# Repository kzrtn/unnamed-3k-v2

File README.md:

# unnamed-3k-v2 keypad
 A simple 3 key mechanical hotswap keypad for osu! Uses an Atmega32u2 (also compatible with Atmega16u2). Created using Kicad and AutoCad/Coreldraw.

 ## IMPORTANT
 This uploaded version of the keypad is **slightly changed** from the prototype in the pictures above.
 
 **Changes:**
 - Removed in-key LEDs
 - Changed north facing switches to south facing
 - Switch pins were changed from B4, B6, B7 to B7, C7, C6
 - Removed unnecessary vias.

This means that what is put up here is **untested**. However if you've tried producing this and everything checks out (it should, changes were very minor) please send me an email at `jolene.tkk@gmail.com` or contact me somehow. I'll update this page and/or fix any issues raised.
 
 ## Features
 - Cherry MX hotswap
 - Uses QMK and has VIA (sort of)
 - 1000hz, chordsplits at 1ms
 - Acrylic sandwich
 - RGB underglow

**Notes regarding QMK and VIA:**

This is not pushed into QMK or VIA's repo. QMK source files are found in the firmware folder. To use VIA with the keypad, go to `settings tab in the VIA software > enable 'Show Design Tab > go to Design tab > Load Draft Definition > Upload the 'load_in_VIA.json' file from qmk-unnamed3kv2-source folder`. **You will have to do this each time you want to use VIA**.

## Settings and RGB modes
Upon plugging in, you will be booted into **Layer 0** where it outputs Z, X and C (play mode). To change RGB modes, hold down the first button (first button on the far left) while plugging in the keypad. It will boot into **Layer 1**.
### Layer 0
| First key  | Second key | Third key |
| ------------- | ------------- |------------- |
| Z | X  | C |
### Layer 1
| First key  | Second key | Third key |
| ------------- | ------------- |------------- |
| Change RGB Mode | Toggle RGB on/off | Go to Layer 2 |
### Layer 2
| First key  | Second key | Third key |
| ------------- | ------------- |------------- |
| Hue value + | Hue value - | Go to Layer 3 |
### Layer 3
| First key  | Second key | Third key |
| ------------- | ------------- |------------- |
| Sat value + | Sat value - | Go to Layer 4 |
### Layer 4
| First key  | Second key | Third key |
| ------------- | ------------- |------------- |
| Brightness value + | Brightness value - | Go to Layer 0 |

**RGB MODES**

- Breathing
- Rainbow mood
- Rainbow swirl
- Static

## Required parts
- PCB with components
- Laser cut acrylic
- 4 x M2 17mm hex stands
- 8 x M2 screws
- (optional) Rubber feet

## PCB assembly tips

The BOM and POS files in `PCB files/Gerber and JLCPCB files` are generated for easy ordering from [JLCPCB](https://jlcpcb.com/). For any parts that are unavailable, especially the crystal and/or the capacitors for the crystal, choose something else that's also 16Mhz with another capacitive load value that's available. Calculate the new values for the caps of the new crystal accordingly using this formula:
```
CL = ((CX1 x CX2) / (CX1 + CX2)) + Cstray

CL: The crystal load capacitance
CX1: The first capacitor
CX2: The second capacitor
Cstray: The stray capacitance in the oscillator circuit, which will normally be in the 2pF to 5pF range.

Assuming that CX1=CX2 then the equation becomes:

CL = ((CX1 x CX1) / (2 x CX1)) + Cstray

CL = (CX1 / 2) + Cstray

Rearranging the equation, we can find the external load capacitor value:

CX1 = 2(CL - Cstray)

For example, if the crystal load capacitance is 15pF, and assuming Cstray=2pF, then:

CX1 = CX2 = 2(15pF - 2pF) = 26pF
```

In the event that you would like to use an **atmega16u2** instead of atmega32u2, you can just do that, no PCB edits is required. But please read the firmware notes section of this readme to adjust the firmware accordingly.

| Part name  | Package type | Notes |
| ------------- | ------------- |------------- |
| Crystal  | SMD3225-4P  | 16MHz is REQUIRED |
| Capacitors  | 0805  |  |
| Resistors | 0805 | |
| Fuse | 1206 | [This](https://lcsc.com/product-detail/Resettable-Fuses_TECHFUSE-nSMD025-24V_C70069.html) is the one I used. Otherwise, ensure your fuse is rated 500mA |
| Kailh hotswap sockets |  | [They're](https://lcsc.com/product-detail/Mechanical-Keyboard-Shaft_Kailh-CPG151101S11_C2803348.html) now available on JLCPCB and LCSC |
| WS2812B (LEDs) |  | Easily found on [JLCPCB](https://lcsc.com/product-detail/Light-Emitting-Diodes-LED_Worldsemi-WS2812B-B-W_C2761795.html) and other websites |
| Tactile switch |  | Easily found on [JLCPCB](https://lcsc.com/product-detail/Tactile-Switches_ALPSALPINE-SKQGABE010_C115351.html) and other websites |

## Acrylic case notes

There are 3 different file formats here. AutoCAD, Coreldraw and PDF.

AutoCAD files are in the 'might be broken and wrong thickness' folder. When I tried exporting the AutoCAD files to .pdf, it would export in the wrong size. I'm not sure if the drawings themselves in the AutoCad files are wrong. They are also outdated, layers are not labelled with the correct thickness, if you use the AutoCAD files, please check the dimensions and the correct the thickness labels to the image shown above (image edited from `new laser cut 16.0.pdf`. The other issue with the AutoCAD file is that the USB cut out size is too big, it will not cover the underside of the USB port properly, if you plan to use AutoCAD, please edit this accordingly.

Coreldraw files are available in latest and 16.0 versions. I'm not sure if both of them are properly up to date (my Coreldraw trial has expired). Please check if they meet the requirements I pointed out in the paragraph above. I'd stick with the `new laser cut 16.0.pdf` file, because that's the last file I used.

**Additional note:** The holes for the hex stands can be quite tight in the `new laser cut 16.0.pdf` file. If they're too tight for your hex stands, enlarge them a little.

For best light diffusion effects, the last layer should use a matte/frosted piece of acrylic. The top of layer can also be matte/frosted for good light diffusion on the top.

## Firmware notes
To flash the firmware, use [QMK toolbox](https://github.com/qmk/qmk_toolbox). Load one of the `.hex` files provided in the `firmware/qmk hex files` folder. `unnamed3kv2_default.hex` does not have (manual) VIA support. `unnamed3kv2_via.hex` has (manual) VIA support. Make sure that the MCU is set to `atmega32u2`, if you are using `atmega16u2`, change it to that instead.

For tinkering with the firmware source, all the files are in `firmware/unnamed3kv2source`. To compile, use QMK MSYS.

**In the case where you are using an atmega16u2**, you'll have to edit the `rules.mk` file in `firmware/unnamed3kv2source`. Change `MCU = atmega32u2` to `MCU = atmega16u2` and recompile the firmware with [QMK MSYS](https://msys.qmk.fm/).

## Printing your own images for decoration
Reuse the same `new laser cut 16.0.pdf` file. Load it into an image editor like Photoshop and put it over whatever image you'd like to use and export it as an image or .pdf then print it out on a piece of paper. **Remember to check fill image to paper size** or similar setting your printer has. Make sure there is no margins so the printed image is the correct size.

**[Print settings example](https://cdn.discordapp.com/attachments/733003518465540278/988617787540930600/print_sizing.png)**

## Learning PCB design with this project
This makes a decent reference, but I don't advise using the same libraries as me because they're outdated and trigger clearance errors in Kicad. Please use [ebalster's keyboard parts library](https://github.com/ebastler/marbastlib) for parts instead.

**Useful resources**
- [My PCB design notes](https://docs.google.com/document/d/1xsjb1sf3pxFw8bXC4gNhWsFhWNOthMoyz6RiJc1UtVI/edit)
- [Best PCB design practices](https://gist.github.com/Sleepdealr/ab05f5edb82eae9e0393f4d63da55adf)

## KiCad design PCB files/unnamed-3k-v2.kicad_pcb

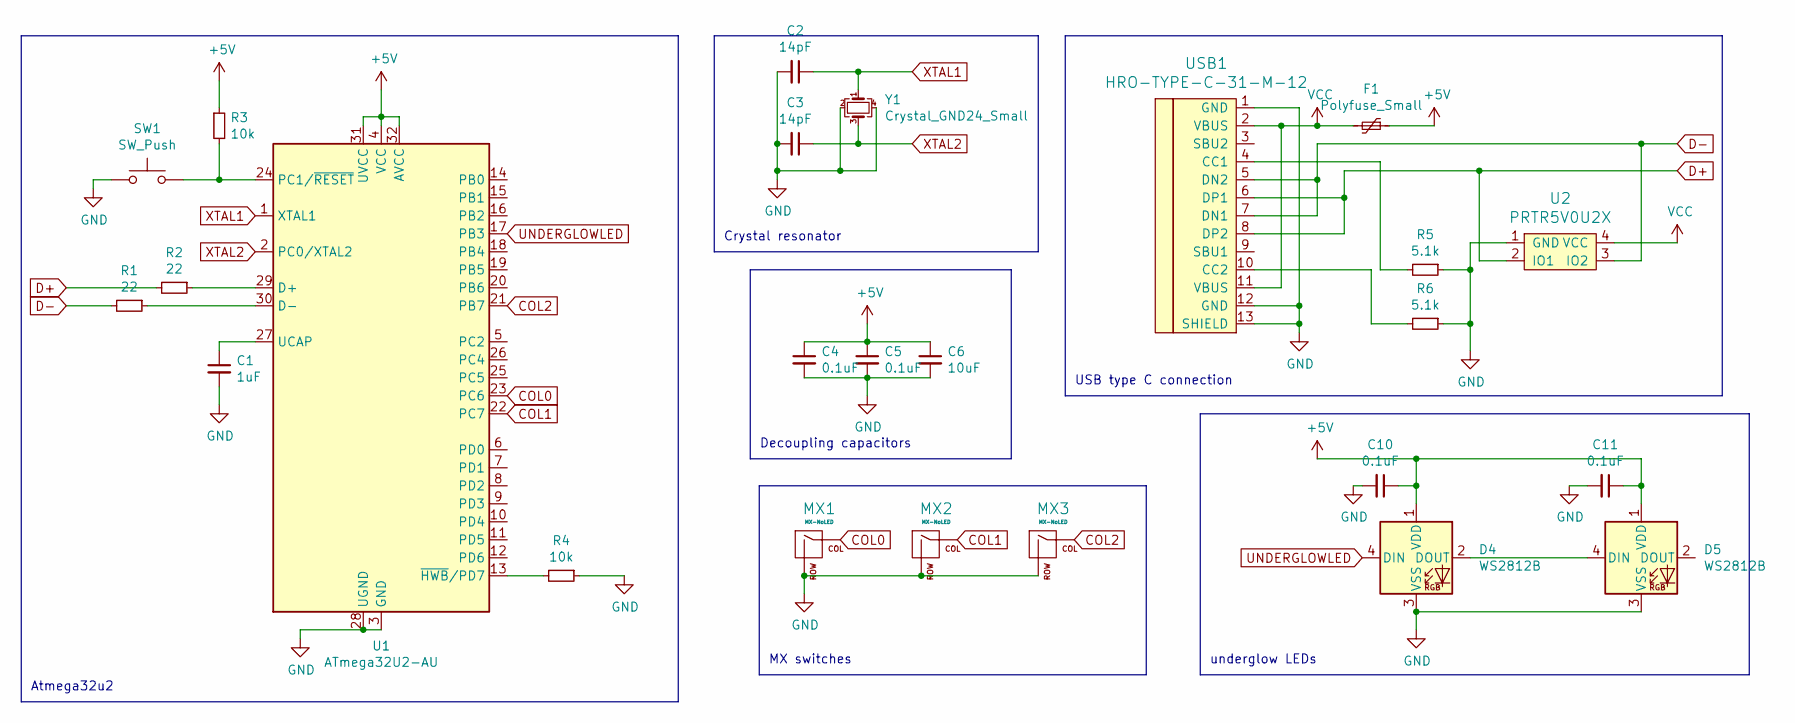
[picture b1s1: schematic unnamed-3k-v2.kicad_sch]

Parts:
C1: 1uF; C_0805_2012Metric_Pad1.15x1.40mm_HandSolder
C2, C3: 14pF; C_0805_2012Metric_Pad1.15x1.40mm_HandSolder
C4, C5, C10, C11: 0.1uF; C_0805_2012Metric_Pad1.15x1.40mm_HandSolder
C6: 10uF; C_0805_2012Metric_Pad1.15x1.40mm_HandSolder
D4, D5: WS2812B; LED_WS2812B_PLCC4_5.0x5.0mm_P3.2mm
F1: Polyfuse_Small; Fuse_1206_3216Metric_Pad1.42x1.75mm_HandSolder
MX1, MX2, MX3: MX-NoLED; MXOnly-1U-Hotswap
R1, R2: 22; R_0805_2012Metric_Pad1.15x1.40mm_HandSolder
R3, R4: 10k; R_0805_2012Metric_Pad1.15x1.40mm_HandSolder
R5, R6: 5.1k; R_0805_2012Metric_Pad1.15x1.40mm_HandSolder
SW1: SW_Push; SKQGADE010
U1: ATmega32U2-AU; TQFP-32_7x7mm_P0.8mm
U2: PRTR5V0U2X; SOT143B
USB1: HRO-TYPE-C-31-M-12; HRO-TYPE-C-31-M-12-HandSoldering
Y1: Crystal_GND24_Small; Crystal_SMD_3225-4Pin_3.2x2.5mm_HandSoldering

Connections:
+5V: C4.1, C5.1, C6.1, C10.1, C11.1, D4.1 (VDD), D5.1 (VDD), F1.1, R3.1, U1.4 (VCC), U1.31 (UVCC), U1.32 (AVCC)
COL0: MX1.1 (COL), U1.23 (PC6)
COL1: MX2.1 (COL), U1.22 (PC7)
COL2: MX3.1 (COL), U1.21 (PB7)
D+: R2.2, U2.2 (IO1), USB1.6 (DP1), USB1.8 (DP2)
D-: R1.2, U2.3 (IO2), USB1.5 (DN2), USB1.7 (DN1)
GND: C1.2, C2.2, C3.2, C4.2, C5.2, C6.2, C10.2, C11.2, D4.3 (VSS), D5.3 (VSS), MX1.2 (ROW), MX2.2 (ROW), MX3.2 (ROW), R4.1, R5.1, R6.1, SW1.1, U1.3 (GND), U1.28 (UGND), U2.1 (GND), USB1.1 (GND), USB1.12 (GND), USB1.13 (SHIELD), Y1.2, Y1.4
unnamed: C1.1, U1.27 (UCAP)
unnamed: D4.2 (DOUT), D5.4 (DIN)
unnamed: R1.1, U1.30 (D-)
unnamed: R2.1, U1.29 (D+)
unnamed: R3.2, SW1.2, U1.24 (PC1/~RESET)
unnamed: R4.2, U1.13 (~HWB/PD7)
unnamed: R5.2, USB1.4 (CC1)
unnamed: R6.2, USB1.10 (CC2)
UNDERGLOWLED: D4.4 (DIN), U1.17 (PB3)
VCC: F1.2, U2.4 (VCC), USB1.2 (VBUS), USB1.11 (VBUS)
XTAL1: C2.1, U1.1 (XTAL1), Y1.1
XTAL2: C3.1, U1.2 (PC0/XTAL2), Y1.3

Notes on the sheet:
Crystal resonator
Atmega32u2
USB type C connection
Decoupling capacitors
underglow LEDs
MX switches

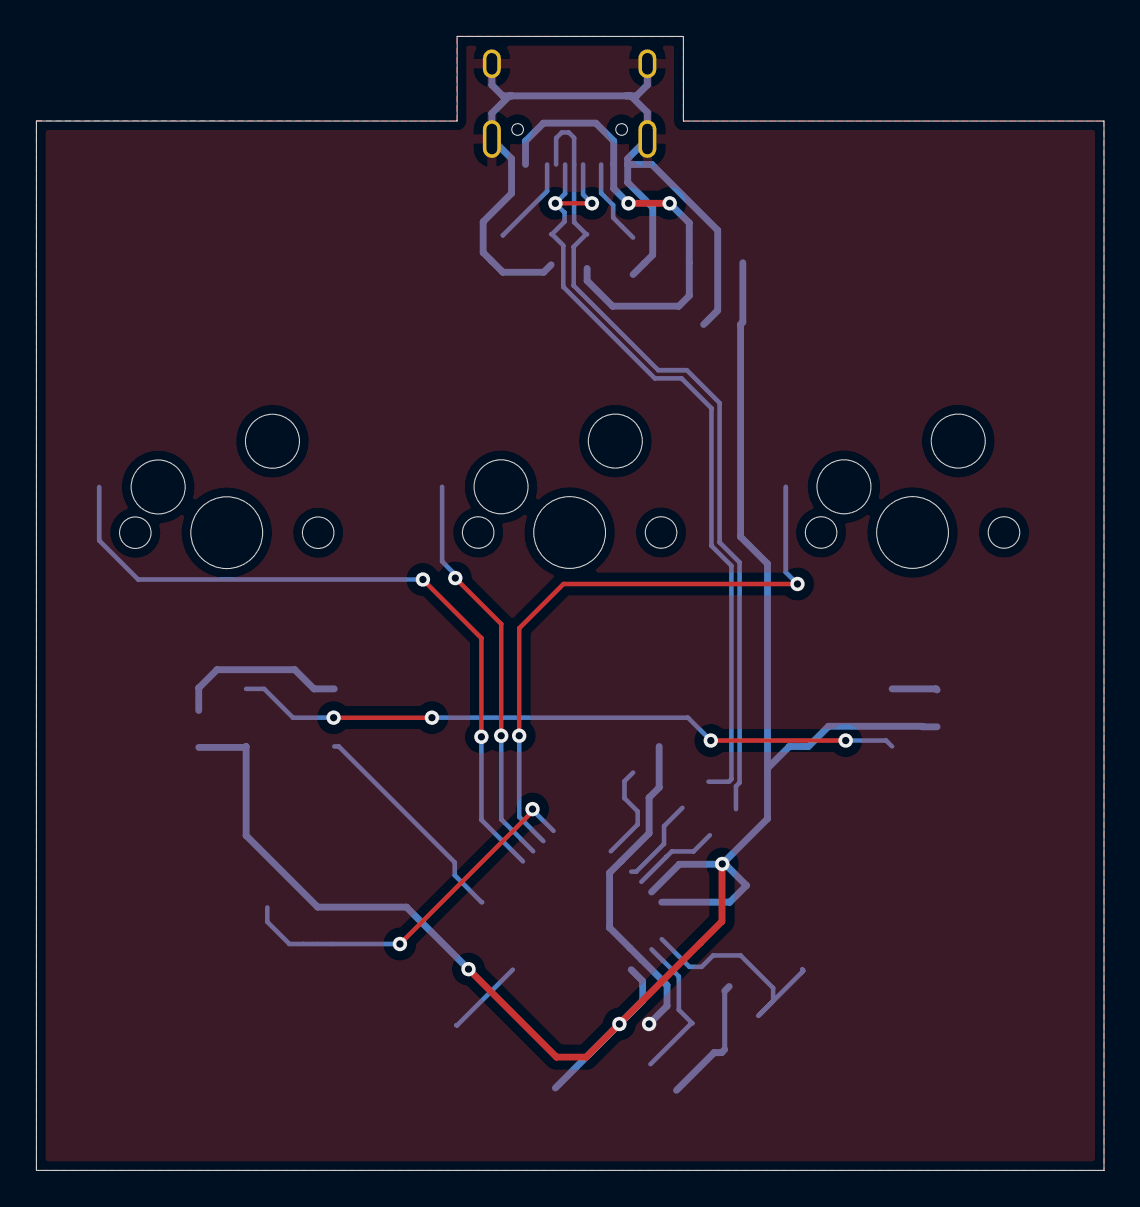
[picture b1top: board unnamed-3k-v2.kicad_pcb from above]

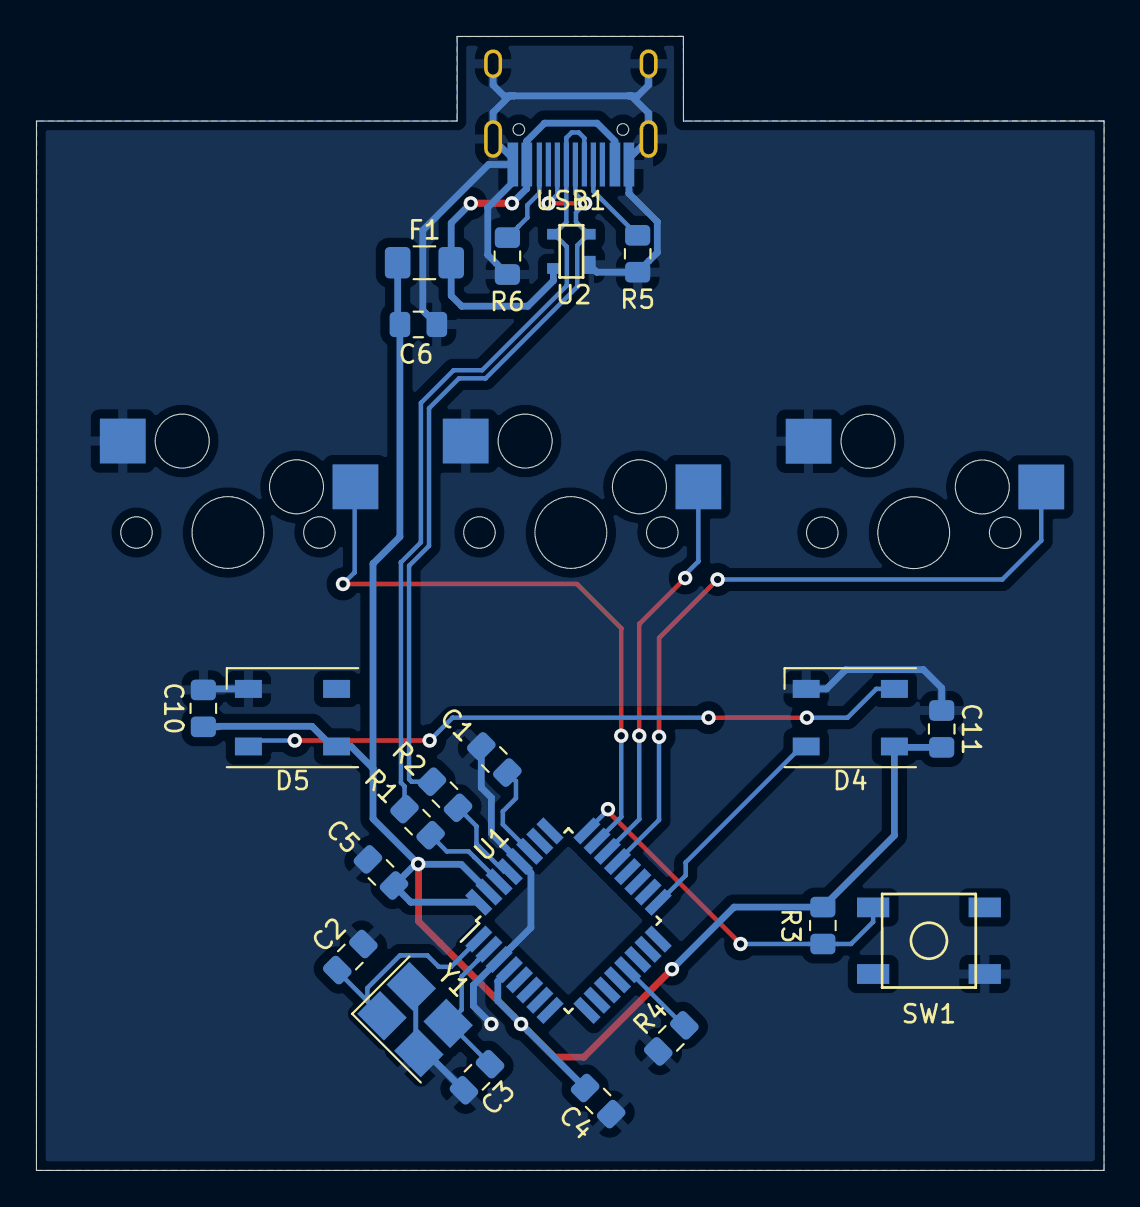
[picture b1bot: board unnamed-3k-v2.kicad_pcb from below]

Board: 2 copper layers, 59.3 x 63.0 mm, 25 parts (22 on the bottom side), 19 nets.

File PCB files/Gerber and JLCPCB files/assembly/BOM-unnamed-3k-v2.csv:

Comment,Designator,Footprint,LCSC
MX-NoLED,MX2,MXOnly-1U-Hotswap,
MX-NoLED,MX3,MXOnly-1U-Hotswap,
MX-NoLED,MX1,MXOnly-1U-Hotswap,
1uF,C1,C_0805_2012Metric_Pad1.15x1.40mm_HandSolder,
10uF,C6,C_0805_2012Metric_Pad1.15x1.40mm_HandSolder,
0.1uF,C11,C_0805_2012Metric_Pad1.15x1.40mm_HandSolder,
10k,R3,R_0805_2012Metric_Pad1.15x1.40mm_HandSolder,
10k,R4,R_0805_2012Metric_Pad1.15x1.40mm_HandSolder,
5.1k,R5,R_0805_2012Metric_Pad1.15x1.40mm_HandSolder,
5.1k,R6,R_0805_2012Metric_Pad1.15x1.40mm_HandSolder,
PRTR5V0U2X,U2,SOT143B,
HRO-TYPE-C-31-M-12,USB1,HRO-TYPE-C-31-M-12-HandSoldering,
ATmega32U2-AU,U1,TQFP-32_7x7mm_P0.8mm,
Polyfuse_Small,F1,Fuse_1206_3216Metric_Pad1.42x1.75mm_HandSolder,
SW_Push,SW1,SKQGADE010,
0.1uF,C5,C_0805_2012Metric_Pad1.15x1.40mm_HandSolder,
WS2812B,D5,LED_WS2812B_PLCC4_5.0x5.0mm_P3.2mm,
0.1uF,C10,C_0805_2012Metric_Pad1.15x1.40mm_HandSolder,
WS2812B,D4,LED_WS2812B_PLCC4_5.0x5.0mm_P3.2mm,
Crystal_GND24_Small,Y1,Crystal_SMD_3225-4Pin_3.2x2.5mm_HandSoldering,
14pF,C3,C_0805_2012Metric_Pad1.15x1.40mm_HandSolder,
14pF,C2,C_0805_2012Metric_Pad1.15x1.40mm_HandSolder,
0.1uF,C4,C_0805_2012Metric_Pad1.15x1.40mm_HandSolder,
22,R2,R_0805_2012Metric_Pad1.15x1.40mm_HandSolder,
22,R1,R_0805_2012Metric_Pad1.15x1.40mm_HandSolder,

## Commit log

2022-01-29 Project Creation
    Created files
2022-01-29 Project Creation
2022-01-29 Add submodules
2022-01-29 Added keyswitch kicad library
2022-01-30 PCB design and laser files finished
2022-02-09 everything else
2022-05-26 Final files
2022-06-20 Fixed PCB and firmware
    Removed in-key RGB and swapped south facing hotswap sockets to north facing
2022-06-21 Updated README.md
    Added rough guide and information for this project
2022-06-21 Removed unnecessary files
2022-11-05 Added atmega16u2 hex file, organized atmega32u2 hex files
    Move the hex files into subfolders denoting which mcu they're for.
    atmega16u2 firmware unfortunately had to have RGB underglow disabled to fit on the atmega16u2. Hoping this can be re-enabled somehow later on.
